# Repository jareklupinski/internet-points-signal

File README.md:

# internet-points-signal
A gadget that lets you know when your standing on the internet has been changed

I designed it mostly to play around in FreeCAD and puzzle out if there are any internet-based statuses that are worth notifying you of using a large green arrow.

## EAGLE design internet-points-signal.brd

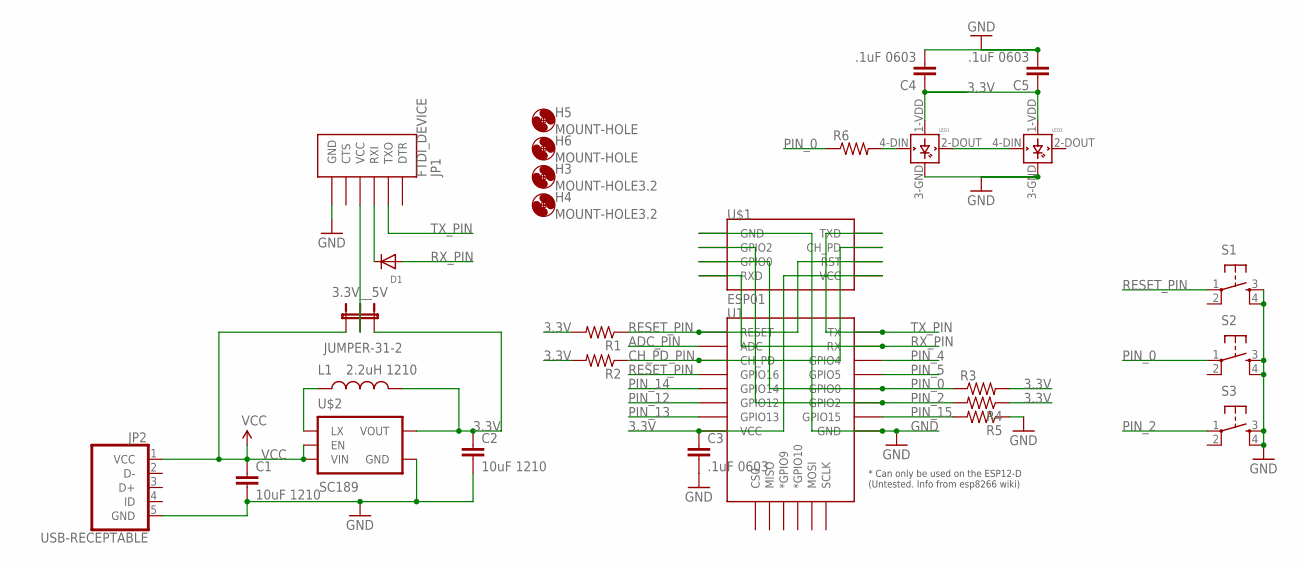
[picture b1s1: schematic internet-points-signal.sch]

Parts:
3.3V__5V: JUMPER-31-2; SJ_3_PASTE1&2
C1, C2: 10uF 1210; 1210
C3, C4, C5: .1uF 0603; 0603-CAP
D1: DIODESOD-323F; SOD-323F
H3, H4: MOUNT-HOLE3.2; 3,2
H5, H6: MOUNT-HOLE; 3,2-DANGER
JP1: FTDI_DEVICE; FTDI_DEVICE_SIDE
JP2: USB-RECEPTABLE; FCI-10103594-0001LF
L1: 2.2uH 1210; 1210
LED1, LED2: WS2812B
R1, R2, R3, R4, R5, R6: RESISTOR0603-RES; 0603-RES
S1, S2, S3: TAC_SWITCHSMD; TACTILE_SWITCH_SMD
U1: ESP12ESMD; ESP12E-SMD
U$1: ESP01
U$2: SC189; SOT23-5

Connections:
3.3V: 3.3V__5V.3, C2.1, C3.1, C4.1, C5.1, L1.2, LED1.1-VDD (VDD), LED2.1-VDD (VDD), R1.2, R2.2, R3.2, R4.1, U1.VCC, U$1.VCC, U$2.4 (VOUT)
ADC_PIN: U1.ADC
CH_PD_PIN: R2.1, U1.CH_PD, U$1.CH_PD
GND: C1.2, C2.2, C3.2, C4.2, C5.2, JP1.P$6 (GND), JP2.5 (GND), LED1.3-GND (GND), LED2.3-GND (GND), R5.1, S1.3, S1.4, S2.3, S2.4, S3.3, S3.4, U1.GND, U$1.GND, U$2.2 (GND)
unnamed: L1.1, U$2.5 (LX)
unnamed: D1.C, JP1.P$3 (RXI)
unnamed: 3.3V__5V.2, JP1.P$4 (VCC)
unnamed: LED1.4-DIN (DIN), R6.2
unnamed: LED1.2-DOUT (DOUT), LED2.4-DIN (DIN)
PIN_0: R3.1, R6.1, S2.1, U1.GPIO0, U$1.GPIO0
PIN_2: R4.2, S3.1, U1.GPIO2, U$1.GPIO2
PIN_4: U1.GPIO4
PIN_5: U1.GPIO5
PIN_12: U1.GPIO12
PIN_13: U1.GPIO13
PIN_14: U1.GPIO14
PIN_15: R5.2, U1.GPIO15
RESET_PIN: R1.1, S1.1, U1.GPIO16, U1.RESET, U$1.RST
RX_PIN: D1.A, U1.RXD0 (RX), U$1.RX (RXD)
TX_PIN: JP1.P$2 (TXO), U1.TXD0 (TX), U$1.TX (TXD)
VCC: 3.3V__5V.1, C1.1, JP2.1 (VCC), U$2.1 (VIN), U$2.3 (EN)

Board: 2 copper layers, 28 parts (2 on the bottom side), 15 nets, no tracks yet.

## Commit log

2018-07-06 work in progress

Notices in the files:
parts and their libraries:
SparkFun-PowerIC: Licensing: CC v3.0 Share-Alike You are welcome to use this library for commercial purposes.
